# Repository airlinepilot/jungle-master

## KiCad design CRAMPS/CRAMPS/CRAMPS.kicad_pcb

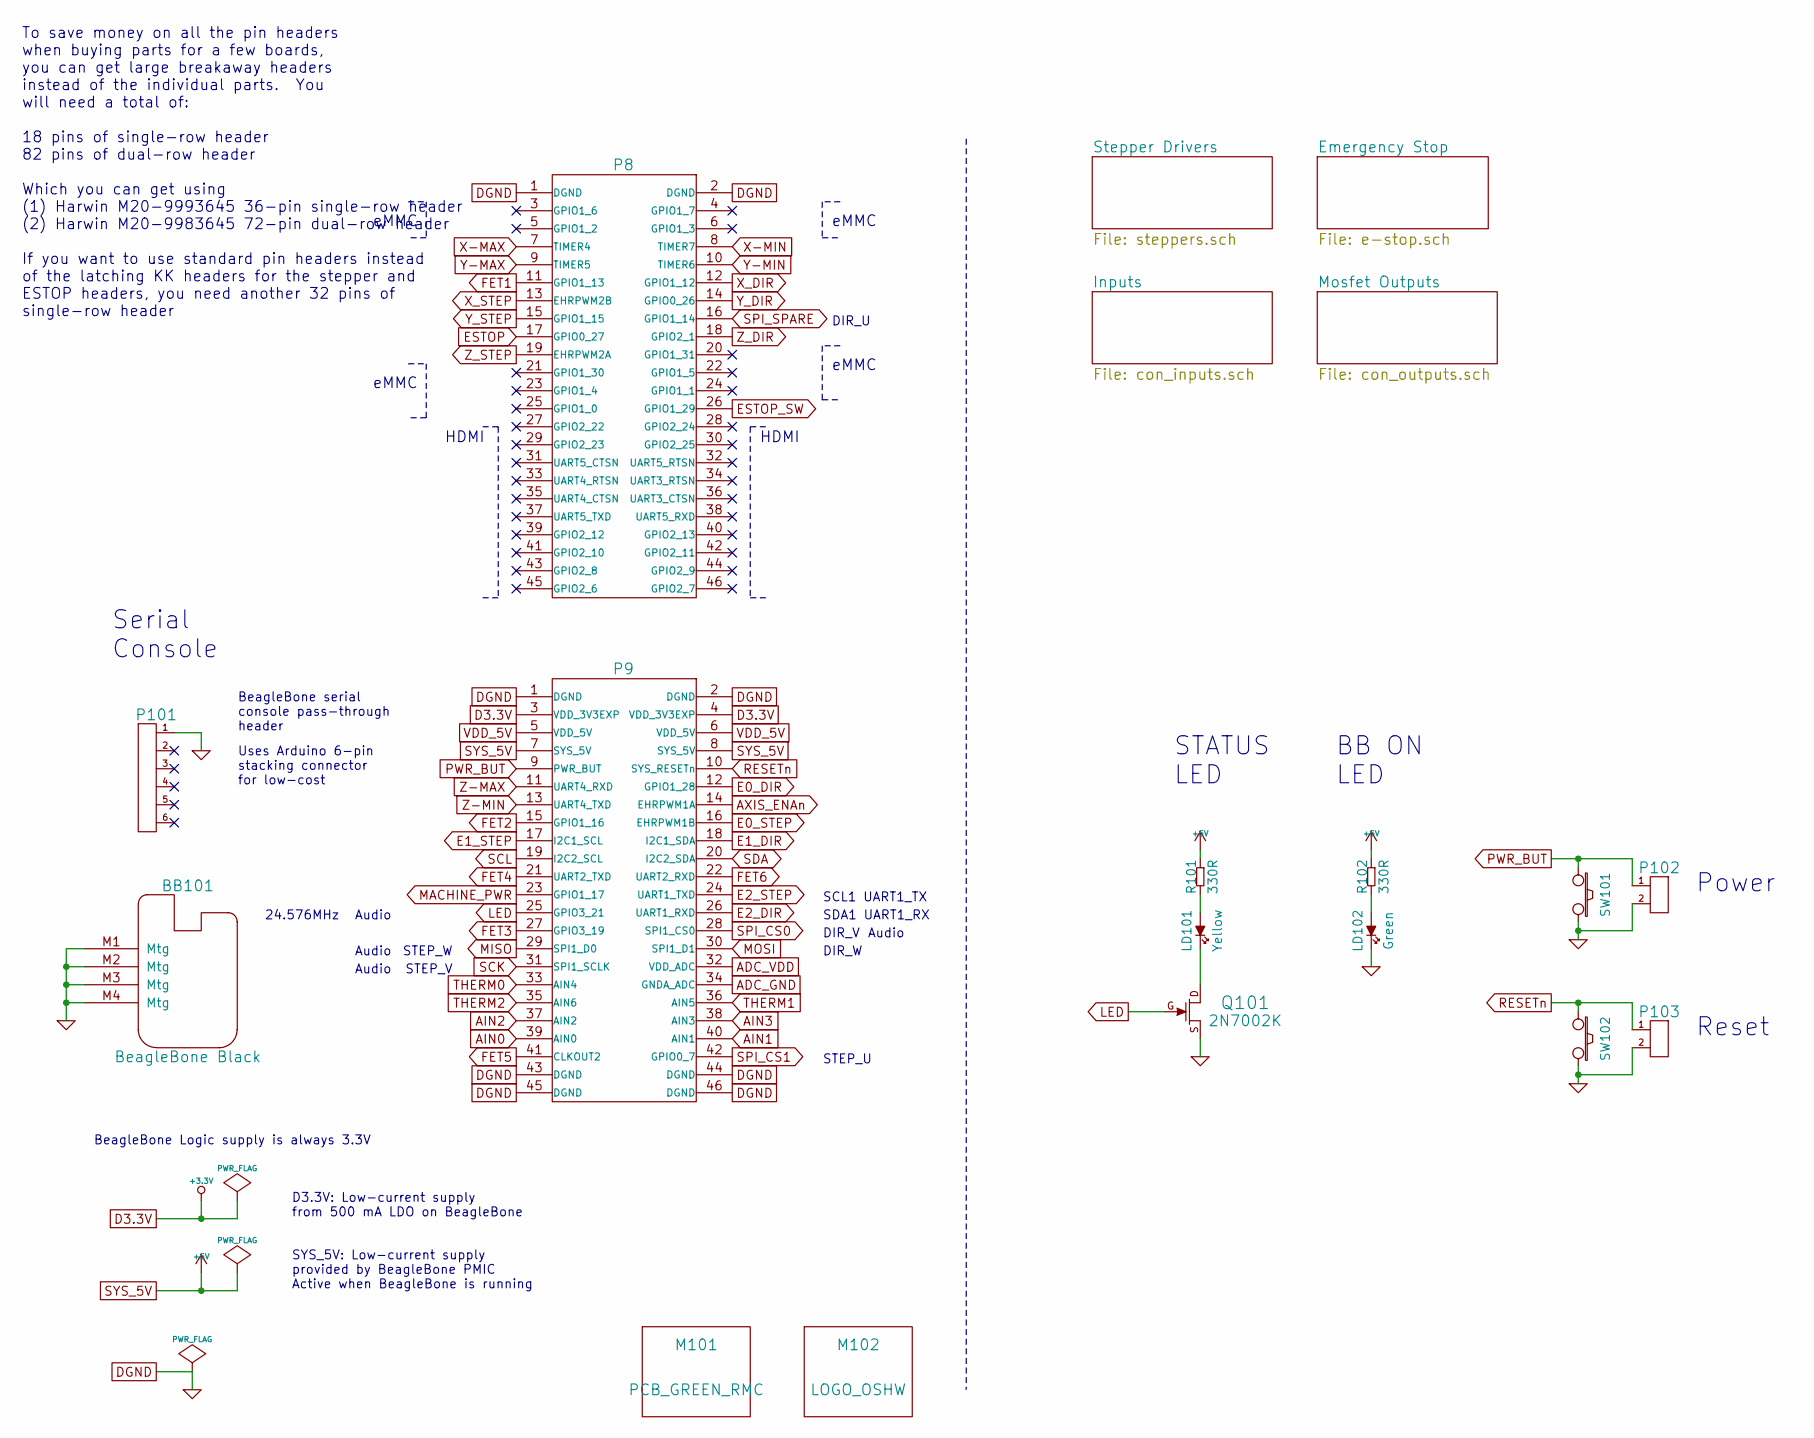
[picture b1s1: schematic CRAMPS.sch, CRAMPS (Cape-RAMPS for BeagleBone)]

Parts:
BB101: BeagleBone Black; BeagleBone-Pins; PartNo BB-BBLK-000
LD101: Yellow; OSRAM-LED-0603; PartNo LY Q976-P1S2-36
LD102: Green; OSRAM-LED-0603; PartNo LG Q971-KN-1
M101: PCB_GREEN_RMC; OSHW_logo_2; PartNo Part of PCB
M102: LOGO_OSHW; PCB_GREEN_RMC; PartNo Part of PCB
P8, P9: BB_EXP_CONN; P8P9_PinHeader; PartNo TSHC-123-D-06-240-GT-LF
P101: SOCKET_6_LONG; pin_strip_6; PartNo PRT-09280
P102, P103: HEADER_2; pin_strip_2; PartNo M20-9990245
Q101: 2N7002K; SOT23GDS; PartNo 2N7002K-7
R101, R102: 330R; RESC1608x55N; PartNo RMCF0603FT330R
SW101, SW102: SW_PUSH; SW_6x6_MULTI; PartNo FSM2JH

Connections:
ADC_GND: P9.34 (GNDA_ADC); also elsewhere on the board
ADC_VDD: P9.32 (VDD_ADC); also elsewhere on the board
AIN0: P9.39 (AIN0); also elsewhere on the board
AIN1: P9.40 (AIN1); also elsewhere on the board
AIN2: P9.37 (AIN2); also elsewhere on the board
AIN3: P9.38 (AIN3); also elsewhere on the board
AXIS_ENAn: P9.14 (EHRPWM1A); also elsewhere on the board
D3.3V: P9.3 (VDD_3V3EXP), P9.4 (VDD_3V3EXP); also elsewhere on the board
E0_DIR: P9.12 (GPIO1_28); also elsewhere on the board
E0_STEP: P9.16 (EHRPWM1B); also elsewhere on the board
E1_DIR: P9.18 (I2C1_SDA); also elsewhere on the board
E1_STEP: P9.17 (I2C1_SCL); also elsewhere on the board
E2_DIR: P9.26 (UART1_RXD); also elsewhere on the board
E2_STEP: P9.24 (UART1_TXD); also elsewhere on the board
ESTOP: P8.17 (GPIO0_27); also elsewhere on the board
ESTOP_SW: P8.26 (GPIO1_29); also elsewhere on the board
FET1: P8.11 (GPIO1_13); also elsewhere on the board
FET2: P9.15 (GPIO1_16); also elsewhere on the board
FET3: P9.27 (GPIO3_19); also elsewhere on the board
FET4: P9.21 (UART2_TXD); also elsewhere on the board
FET5: P9.41 (CLKOUT2); also elsewhere on the board
FET6: P9.22 (UART2_RXD); also elsewhere on the board
LED: P9.25 (GPIO3_21), Q101.G
MACHINE_PWR: P9.23 (GPIO1_17); also elsewhere on the board
MISO: P9.29 (SPI1_D0); also elsewhere on the board
MOSI: P9.30 (SPI1_D1); also elsewhere on the board
unnamed: LD102.A, R102.2
unnamed: LD101.A, R101.2
unnamed: LD101.K, Q101.D
PWR_BUT: P9.9 (PWR_BUT), P102.1, SW101.1
RESETn: P9.10 (SYS_RESETn), P103.1, SW102.1
SCK: P9.31 (SPI1_SCLK); also elsewhere on the board
SCL: P9.19 (I2C2_SCL); also elsewhere on the board
SDA: P9.20 (I2C2_SDA); also elsewhere on the board
SPI_CS0: P9.28 (SPI1_CS0); also elsewhere on the board
SPI_CS1: P9.42 (GPIO0_7); also elsewhere on the board
SPI_SPARE: P8.16 (GPIO1_14); also elsewhere on the board
SYS_5V: P9.7 (SYS_5V), P9.8 (SYS_5V), R101.1, R102.1; also elsewhere on the board
THERM0: P9.33 (AIN4); also elsewhere on the board
THERM1: P9.36 (AIN5); also elsewhere on the board
THERM2: P9.35 (AIN6); also elsewhere on the board
X-MAX: P8.7 (TIMER4); also elsewhere on the board
X-MIN: P8.8 (TIMER7); also elsewhere on the board
X_DIR: P8.12 (GPIO1_12); also elsewhere on the board
X_STEP: P8.13 (EHRPWM2B); also elsewhere on the board
Y-MAX: P8.9 (TIMER5); also elsewhere on the board
Y-MIN: P8.10 (TIMER6); also elsewhere on the board
Y_DIR: P8.14 (GPIO0_26); also elsewhere on the board
Y_STEP: P8.15 (GPIO1_15); also elsewhere on the board
Z-MAX: P9.11 (UART4_RXD); also elsewhere on the board
Z-MIN: P9.13 (UART4_TXD); also elsewhere on the board
Z_DIR: P8.18 (GPIO2_1); also elsewhere on the board
Z_STEP: P8.19 (EHRPWM2A); also elsewhere on the board

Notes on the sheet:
STATUS LED
HDMI
eMMC
24.576MHz
Audio
BeagleBone serial console pass-through header
SCL1 UART1_TX
SDA1 UART1_RX
To save money on all the pin headers when buying parts for a few boards, you can get large breakaway headers instead of the individual parts. You will need a total of: 18 pins of single-row header 82 pins of dual-row header Which you can get using (1) Harwin M20-9993645 36-pin single-row header (2)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
BB ON LED
BeagleBone Logic supply is always 3.3V
SYS_5V: Low-current supply provided by BeagleBone PMIC Active when BeagleBone is running
D3.3V: Low-current supply from 500 mA LDO on BeagleBone
Serial Console
Uses Arduino 6-pin stacking connector for low-cost
Power
Reset
STEP_U
STEP_V
STEP_W
DIR_U
DIR_V
DIR_W

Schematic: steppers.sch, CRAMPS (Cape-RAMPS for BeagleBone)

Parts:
C201, C202, C203, C204, C205, C206: 100u 35V; c_elec_6.3x7.7; PartNo UCD1V101MCL6GS
F201: 10A; Fuse-Loose; PartNo 0297010.WXNV
FH201: FUSE-HOLDER; Keystone-3568; PartNo 3568
JP201, JP202, JP203, JP204, JP205, JP206: HEADER_3X2; pin_strip_3x2; PartNo M20-9980345
P201: PT_2,5-2-5,0-H; PartNo 1935776
P202, P203, P204, P205, P206, P207: KK-2.54-4W; CONN_KK_2.54_4W; PartNo 22-23-2041
P208, P209, P210, P211: POLOLU_SOCKET; Pololu_Socket; PartNo PPTC241LFBN-RC
R201, R202, R203, R204, R205, R206: 100k; RESC1608x55N; PartNo RMCF0603FT100K
S201, S202, S203, S204, S205, S206, S207, S208, S209, S210, S211, S212, S213, S214, S215, S216, S217, S218: SHUNT; Shunt; PartNo 382811-8
U201, U202, U203, U204, U205, U206: Pololu; POLOLU; PartNo DRV8825

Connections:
+V_MOTOR: C201.1, C202.1, C203.1, C204.1, C205.1, C206.1, FH201.3, FH201.4, U201.16, U202.16, U203.16, U204.16, U205.16, U206.16; also elsewhere on the board
/Stepper Drivers/E01A: P205.3, U204.12
/Stepper Drivers/E01B: P205.4, U204.11
/Stepper Drivers/E02A: P205.2, U204.13
/Stepper Drivers/E02B: P205.1, U204.14
/Stepper Drivers/E11A: P206.3, U205.12
/Stepper Drivers/E11B: P206.4, U205.11
/Stepper Drivers/E12A: P206.2, U205.13
/Stepper Drivers/E12B: P206.1, U205.14
/Stepper Drivers/E21A: P207.3, U206.12
/Stepper Drivers/E21B: P207.4, U206.11
/Stepper Drivers/E22A: P207.2, U206.13
/Stepper Drivers/E22B: P207.1, U206.14
/Stepper Drivers/MOT_IN: FH201.1, FH201.2, P201.1
/Stepper Drivers/X1A: P202.3, U201.12
/Stepper Drivers/X1B: P202.4, U201.11
/Stepper Drivers/X2A: P202.2, U201.13
/Stepper Drivers/X2B: P202.1, U201.14
/Stepper Drivers/Y1A: P203.3, U202.12
/Stepper Drivers/Y1B: P203.4, U202.11
/Stepper Drivers/Y2A: P203.2, U202.13
/Stepper Drivers/Y2B: P203.1, U202.14
/Stepper Drivers/Z1A: P204.3, U203.12
/Stepper Drivers/Z1B: P204.4, U203.11
/Stepper Drivers/Z2A: P204.2, U203.13
/Stepper Drivers/Z2B: P204.1, U203.14
D3.3V: JP201.2, JP201.4, JP201.6, JP202.2, JP202.4, JP202.6, JP203.2, JP203.4, JP203.6, JP204.2, JP204.4, JP204.6, JP205.2, JP205.4, JP205.6, JP206.2, JP206.4, JP206.6, U201.5, U201.6, U201.10, U202.5, U202.6, U202.10, U203.5, U203.6, U203.10, U204.5, U204.6, U204.10, U205.5, U205.6, U205.10, U206.5, U206.6, U206.10; also elsewhere on the board
E0_DIR: U204.8; also elsewhere on the board
E0_EN_BUFn: U201.1, U202.1, U203.1, U204.1, U205.1, U206.1; also elsewhere on the board
E0_STEP: U204.7; also elsewhere on the board
E1_DIR: U205.8; also elsewhere on the board
E1_STEP: U205.7; also elsewhere on the board
E2_DIR: U206.8; also elsewhere on the board
E2_STEP: U206.7; also elsewhere on the board
unnamed: JP202.5, U202.4
unnamed: JP201.5, U201.4
unnamed: JP201.3, U201.3
unnamed: JP205.5, U205.4
unnamed: JP205.3, U205.3
unnamed: JP204.5, U204.4
unnamed: JP204.3, U204.3
unnamed: JP201.1, R201.1, U201.2
unnamed: JP206.3, U206.3
unnamed: JP206.5, U206.4
unnamed: JP202.1, R202.1, U202.2
unnamed: JP203.1, R203.1, U203.2
unnamed: JP205.1, R205.1, U205.2
unnamed: JP204.1, R204.1, U204.2
unnamed: JP206.1, R206.1, U206.2
unnamed: JP203.5, U203.4
unnamed: JP203.3, U203.3
unnamed: JP202.3, U202.3
X_DIR: U201.8; also elsewhere on the board
X_STEP: U201.7; also elsewhere on the board
Y_DIR: U202.8; also elsewhere on the board
Y_STEP: U202.7; also elsewhere on the board
Z_DIR: U203.8; also elsewhere on the board
Z_STEP: U203.7; also elsewhere on the board

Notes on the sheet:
Motor Power 12-24V, 10A
24-pin Single-Row sockets for Pololus
Shunts to set micro-stepping

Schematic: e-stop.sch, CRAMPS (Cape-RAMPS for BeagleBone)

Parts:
C301, C302: 100n; CAPC1608x55N; PartNo GRM188R71C104KA01D
JP301: HEADER_2X2; pin_strip_2x2; PartNo M20-9980245
LD301: Green; OSRAM-LED-0603; PartNo LG Q971-KN-1
LD302: Red; OSRAM-LED-0603; PartNo LS Q976-NR-1
P301: HEADER_2; pin_strip_2; PartNo M20-9990245
P302: KK-2.54-2W; CONN_KK_2.54_2W; PartNo 22-23-2021
P303: HEADER_4X2; pin_strip_4x2; PartNo M20-9980445
P304: HEADER_3X2; pin_strip_3x2; PartNo M20-9980345
P305: HEADER_6; pin_strip_6; PartNo M20-9990645
Q301, Q302, Q303, Q304, Q305: 2N7002K; SOT23GDS; PartNo 2N7002K-7
R301, R308, R309, R310, R311, R312, R313, R315, R316: 10k; RESC1608x55N; PartNo RMCF0603FT10K0
R302: 2K7; RESC1608x55N; PartNo RMCF0603FT2K70
R303: 330R; RESC1608x55N; PartNo RMCF0603FT330R
R304, R306, R307, R314: 4k7; RESC1608x55N; PartNo RMCF0603FT4K70
R305: 220R; RESC1608x55N; PartNo RMCF0603FT220R
S301: SHUNT; Shunt; PartNo 382811-8
U301: 24C256; SOIC127P600X175-8AN; PartNo CAT24C256WI-GT3
U302: 74ACT244; SOIC127P1032X265-20N; PartNo 74ACT244SCX

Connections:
+V_MOTOR: P304.1, P304.3, P304.5; also elsewhere on the board
/Emergency Stop/MACHINE_PWRn: LD301.K, Q304.D, R308.2, U302.1 (~1G), U302.19 (~2G)
/Emergency Stop/PS-On: P301.1, Q302.D
ADC_GND: P305.5; also elsewhere on the board
ADC_VDD: P305.6; also elsewhere on the board
AIN0: P305.4; also elsewhere on the board
AIN1: P305.2; also elsewhere on the board
AIN2: P305.1; also elsewhere on the board
AIN3: P305.3; also elsewhere on the board
AXIS_ENAn: U302.2 (1A1), U302.4 (1A2); also elsewhere on the board
D3.3V: C301.1, JP301.1, JP301.3, P303.2, R301.1, R304.1, R305.1, R306.1, R307.1, R310.1, R314.1, U301.3 (A2), U301.8 (VCC); also elsewhere on the board
E0_EN_BUFn: R314.2, U302.18 (1Y1); also elsewhere on the board
EN_CRAMP3n: P303.8, R310.2, U302.16 (1Y2)
ESTOP: R302.2; also elsewhere on the board
ESTOP_SW: Q301.G; also elsewhere on the board
FET1: U302.17 (2A4); also elsewhere on the board
FET1_BUF: R309.1, U302.3 (2Y4); also elsewhere on the board
FET2: U302.15 (2A3); also elsewhere on the board
FET2_BUF: R311.1, U302.5 (2Y3); also elsewhere on the board
FET3: U302.13 (2A2); also elsewhere on the board
FET3_BUF: R312.1, U302.7 (2Y2); also elsewhere on the board
FET4: U302.11 (2A1); also elsewhere on the board
FET4_BUF: R313.1, U302.9 (2Y1); also elsewhere on the board
FET5: U302.6 (1A3); also elsewhere on the board
FET5_BUF: R316.1, U302.14 (1Y3); also elsewhere on the board
FET6: U302.8 (1A4); also elsewhere on the board
FET6_BUF: R315.1, U302.12 (1Y4); also elsewhere on the board
MACHINE_PWR: Q302.G, Q304.G; also elsewhere on the board
unnamed: JP301.2, U301.7 (WP)
unnamed: LD302.A, R305.2
unnamed: P302.1, Q302.S, Q304.S, Q305.G, R302.1, R304.2
unnamed: LD302.K, Q305.D
unnamed: Q301.D, Q303.G, R301.2
unnamed: P302.2, Q303.D
unnamed: LD301.A, R303.2
unnamed: JP301.4, U301.1 (A0)
SCL: P303.3, R306.2, U301.6 (SCL); also elsewhere on the board
SDA: P303.5, R307.2, U301.5 (SDA); also elsewhere on the board
SPI_CS1: P303.4; also elsewhere on the board
SPI_SPARE: P303.6; also elsewhere on the board
SYS_5V: C302.1, P303.1, R303.1, R308.1, U302.20 (VDD); also elsewhere on the board

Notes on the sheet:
Emergency Stop switch (Normally Closed type) use shunt if not present
Active low
Active high
Must use ACT type buffer with 24 mA output drive Inputs are compatible with 3.3V or 5V logic
Each Pololu has a 100K pull-down on the enable line. Make sure the pull up will reach a valid logic level (2.2V or more) with multiple enables paralleled.
ESTOP Active (high) unless: * ESTOP chain is unbroken * Software is driving ESTOP_SW low
Machine Power Status LED
EEPROM
Address and WP pins have internal pull-down Default configuration is no shunts populated: Addr = 0xA8 WP = Disabled (writes allowed)
I2C and misc signals
Analog
Resistive Touch Screen
ATX Power On
Two FETs used to keep ESTOP polarity consistent with V1.0
ESTOP
Place a shunt on ESTOP header by default, for folks who do not have an off-board ESTOP switch
Motor Power
CRAMP3 Expansion
Series resistor on ESTOPn provides some protection from ESTOP chain FETs protect against high voltage from PS_ON or MACHINE_PWRn feeding back to the 3.3V 'Bone
ACTIVE
Status LED
STEP_U
DIR_U

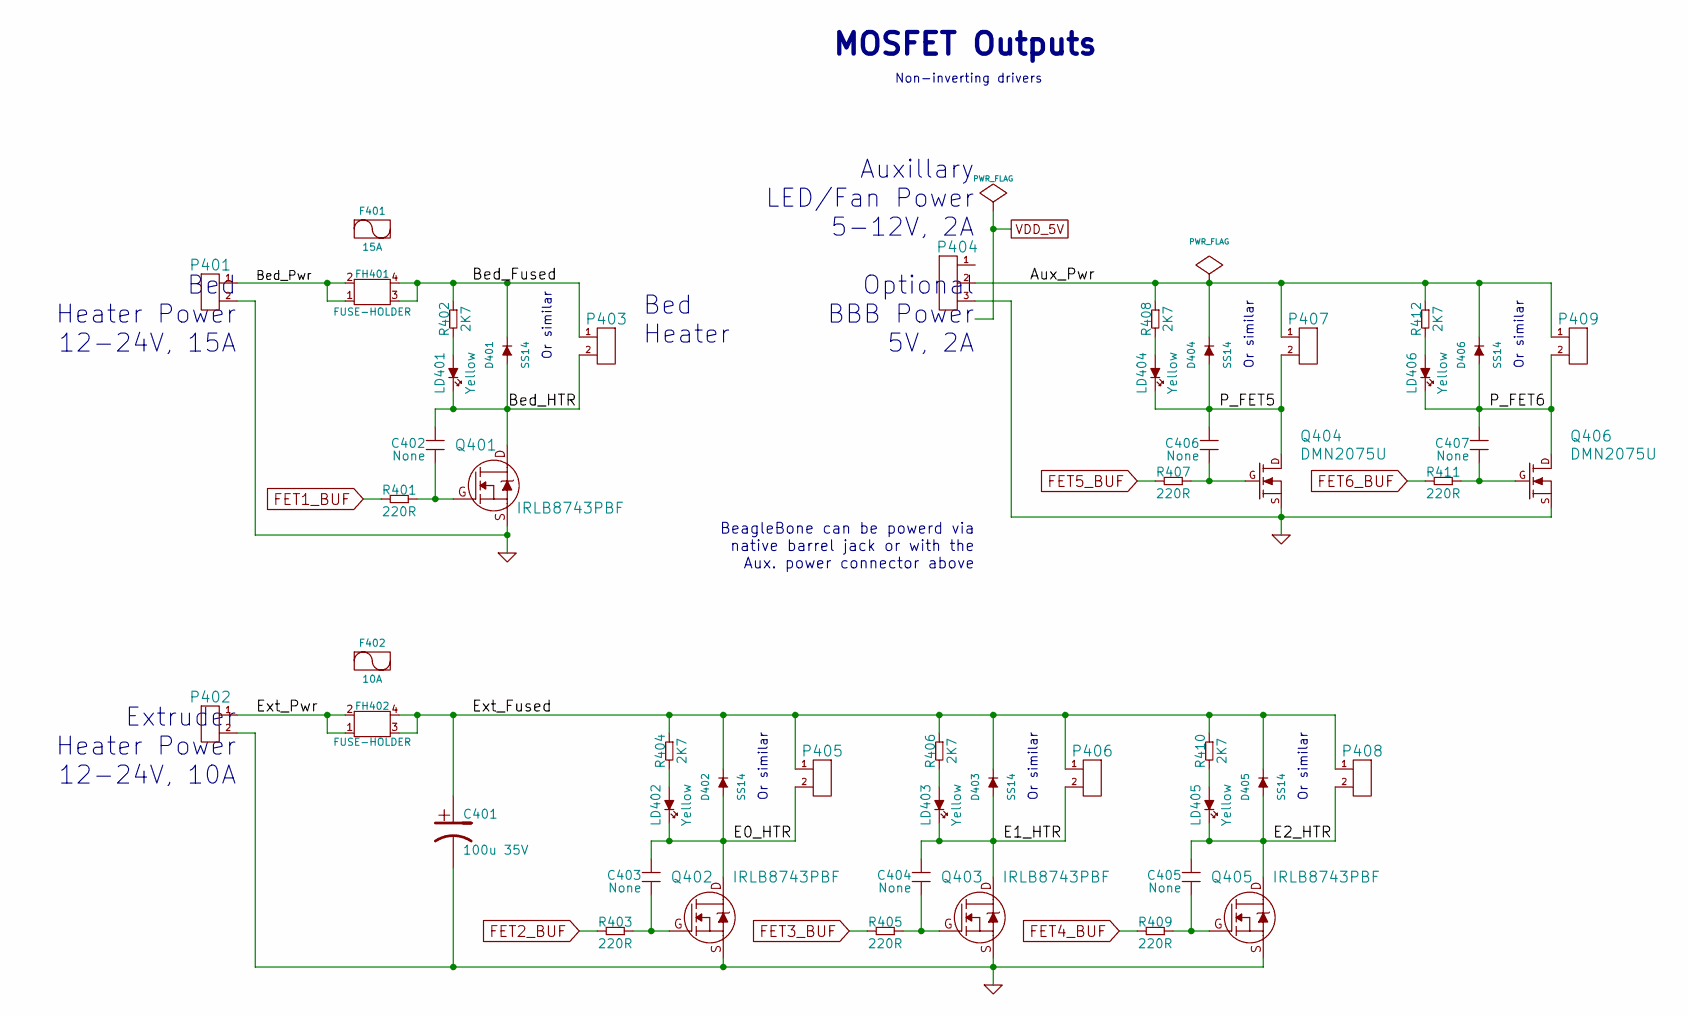
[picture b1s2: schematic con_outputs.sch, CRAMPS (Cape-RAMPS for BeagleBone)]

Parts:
C401: 100u 35V; c_elec_6.3x7.7; PartNo UCD1V101MCL6GS
C402, C403, C404, C405, C406, C407: None; CAPC1608x55N; PartNo Do Not Populate
D401, D402, D403, D404, D405, D406: SS14; DIOM5127X229N; PartNo SS14-E3/61T
F401: 15A; Fuse-Loose; PartNo 0297015.WXNV
F402: 10A; Fuse-Loose; PartNo 0297010.WXNV
FH401, FH402: FUSE-HOLDER; Keystone-3568; PartNo 3568
LD401, LD402, LD403, LD404, LD405, LD406: Yellow; OSRAM-LED-0603; PartNo LY Q976-P1S2-36
P401, P402, P403: PT_2,5-2-5,0-H; PartNo 1935776
P404: PT_1,5-3-3,5-H; PartNo 1984620
P405, P406, P408: PT_1,5-2-3,5-H; PartNo 1984617
P407, P409: KK-2.54-2W; CONN_KK_2.54_2W; PartNo 22-23-2021
Q401, Q402, Q403, Q405: IRLB8743PBF; TO-220AB_IRF2804_RMC; PartNo IRLB8743PBF
Q404, Q406: DMN2075U; SOT23GDS; PartNo DMN2075U-7
R401, R403, R405, R407, R409, R411: 220R; RESC1608x55N; PartNo RMCF0603FT220R
R402, R404, R406, R408, R410, R412: 2K7; RESC1608x55N; PartNo RMCF0603FT2K70

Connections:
/Mosfet Outputs/Bed_Fused: D401.K, FH401.3, FH401.4, P403.1, R402.1
/Mosfet Outputs/Bed_HTR: C402.1, D401.A, LD401.K, P403.2, Q401.D
/Mosfet Outputs/Bed_Pwr: FH401.1, FH401.2, P401.1
/Mosfet Outputs/E0_HTR: C403.1, D402.A, LD402.K, P405.2, Q402.D
/Mosfet Outputs/E1_HTR: C404.1, D403.A, LD403.K, P406.2, Q403.D
/Mosfet Outputs/E2_HTR: C405.1, D405.A, LD405.K, P408.2, Q405.D
/Mosfet Outputs/Ext_Fused: C401.1, D402.K, D403.K, D405.K, FH402.3, FH402.4, P405.1, P406.1, P408.1, R404.1, R406.1, R410.1
/Mosfet Outputs/Ext_Pwr: FH402.1, FH402.2, P402.1
/Mosfet Outputs/P_FET5: C406.1, D404.A, LD404.K, P407.2, Q404.D
/Mosfet Outputs/P_FET6: C407.1, D406.A, LD406.K, P409.2, Q406.D
FET1_BUF: R401.2; also elsewhere on the board
FET2_BUF: R403.2; also elsewhere on the board
FET3_BUF: R405.2; also elsewhere on the board
FET4_BUF: R409.2; also elsewhere on the board
FET5_BUF: R407.2; also elsewhere on the board
FET6_BUF: R411.2; also elsewhere on the board
unnamed: LD402.A, R404.2
unnamed: LD405.A, R410.2
unnamed: LD404.A, R408.2
unnamed: LD403.A, R406.2
unnamed: LD401.A, R402.2
unnamed: LD406.A, R412.2
unnamed: C404.2, Q403.G, R405.1
unnamed: C403.2, Q402.G, R403.1
unnamed: C407.2, Q406.G, R411.1
unnamed: C406.2, Q404.G, R407.1
unnamed: C402.2, Q401.G, R401.1
unnamed: C405.2, Q405.G, R409.1

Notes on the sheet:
Non-inverting drivers
MOSFET Outputs
Or similar
Bed Heater Power 12-24V, 15A
Bed Heater
Extruder Heater Power 12-24V, 10A
Auxillary LED/Fan Power 5-12V, 2A Optional BBB Power 5V, 2A
BeagleBone can be powerd via native barrel jack or with the Aux. power connector above

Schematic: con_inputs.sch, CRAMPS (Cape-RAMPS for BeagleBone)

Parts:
C501, C502, C503, C504, C505: 100n; CAPC1608x55N; PartNo GRM188R71C104KA01D
C506, C507, C508, C509: 10u; CAPC1608x55N; PartNo JMK107ABJ106MAHT
JP501: HEADER_2; pin_strip_2; PartNo M20-9990245
P501: HEADER_6; pin_strip_6; PartNo M20-9990645
P502: HEADER_6X2; pin_strip_6x2; PartNo M20-9980645
P503, P504: HEADER_4X2; pin_strip_4x2; PartNo M20-9980445
R501, R502, R503, R504, R505, R506, R507, R508, R509, R510: 10k; RESC1608x55N; PartNo RMCF0603FT10K0
R511, R512, R513, R514: 2K0 1%; RESC1608x55N; PartNo RMCF0603FT2K00
R515, R516, R517, R518: 4k7; RESC1608x55N; PartNo RMCF0603FT4K70
S501: SHUNT; Shunt; PartNo 382811-8
U501: 74CBTD3861; SOIC127P1030X265-24N

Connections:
/Inputs/MISO-5V: P503.2, R507.2, U501.8 (A7)
/Inputs/MOSI-5V: P503.6, R509.2, U501.10 (A9)
/Inputs/SCK-5V: P503.4, R508.2, U501.9 (A8)
/Inputs/SPI_CS0-5V: P503.8, R510.2, U501.11 (A10)
ADC_GND: C502.2, C503.2, C504.2, C505.2, C506.2, C507.2, C508.2, C509.2, P504.1, P504.3, P504.5, P504.7; also elsewhere on the board
ADC_VDD: R511.1, R512.1, R513.1, R514.1; also elsewhere on the board
AIN3: JP501.2; also elsewhere on the board
MISO: U501.16 (B7); also elsewhere on the board
MOSI: U501.14 (B9); also elsewhere on the board
unnamed: P504.4, R513.2, R517.2
unnamed: P504.8, R511.2, R515.2
unnamed: P504.2, R514.2, R518.2
unnamed: P502.4, R502.2, U501.3 (A2)
unnamed: P502.6, R503.2, U501.4 (A3)
unnamed: P502.8, R504.2, U501.5 (A4)
unnamed: P502.10, R505.2, U501.6 (A5)
unnamed: P502.12, R506.2, U501.7 (A6)
unnamed: P502.2, R501.2, U501.2 (A1)
unnamed: P504.6, R512.2, R516.2
SCK: U501.15 (B8); also elsewhere on the board
SPI_CS0: U501.13 (B10); also elsewhere on the board
SYS_5V: C501.1, P501.1, P501.2, P501.3, P501.4, P501.5, P501.6, R501.1, R502.1, R503.1, R504.1, R505.1, R506.1, R507.1, R508.1, R509.1, R510.1, U501.24 (VCC); also elsewhere on the board
THERM0: C502.1, C506.1, R515.1; also elsewhere on the board
THERM1: C503.1, C507.1, R516.1; also elsewhere on the board
THERM2: C504.1, C508.1, R517.1; also elsewhere on the board
THERM3: C505.1, C509.1, JP501.1, R518.1
X-MAX: U501.21 (B2); also elsewhere on the board
X-MIN: U501.22 (B1); also elsewhere on the board
Y-MAX: U501.19 (B4); also elsewhere on the board
Y-MIN: U501.20 (B3); also elsewhere on the board
Z-MAX: U501.17 (B6); also elsewhere on the board
Z-MIN: U501.18 (B5); also elsewhere on the board

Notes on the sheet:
Endstop inputs are 5V tolerant and may also be used as 3.3V output signals if desired
Endstops
From Thermistors
Thermistor Inputs
Shunt populated by default Remove to support 4-wire touch-screen using AIN 0-3
To ADC Inputs
P503 may be used for: * Additional digital I/O * CRAMP3 add-on board * SPI expansion
STEP_V
STEP_W
DIR_V
DIR_W

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
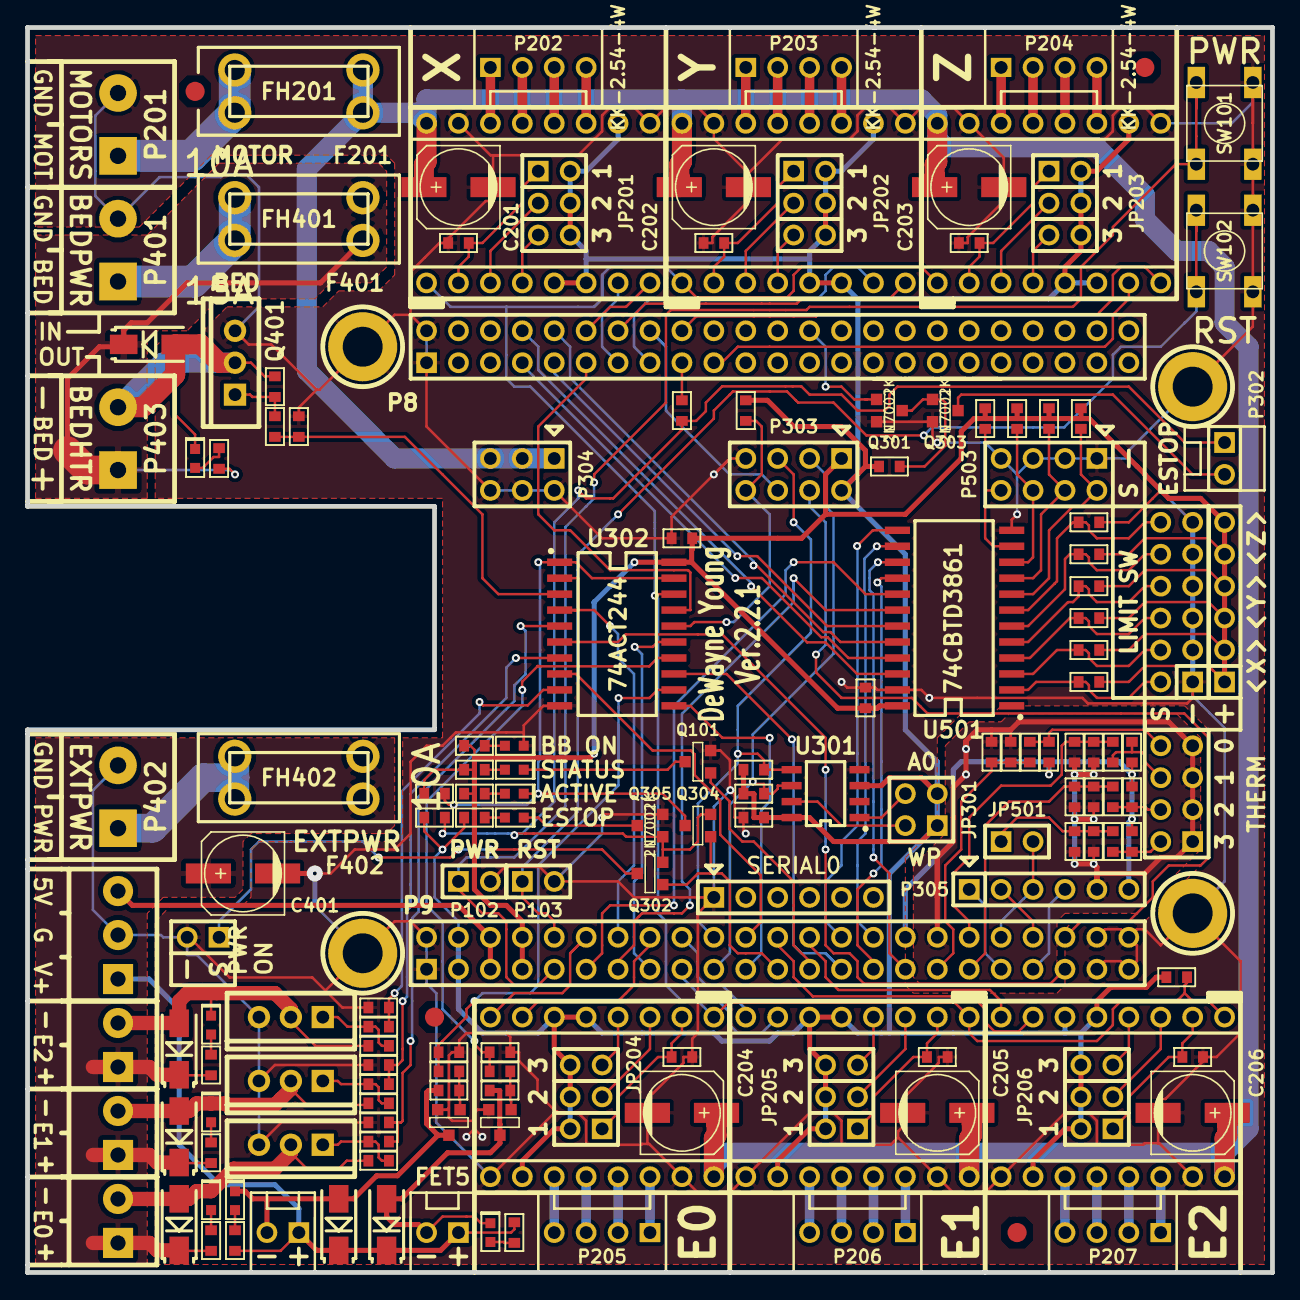
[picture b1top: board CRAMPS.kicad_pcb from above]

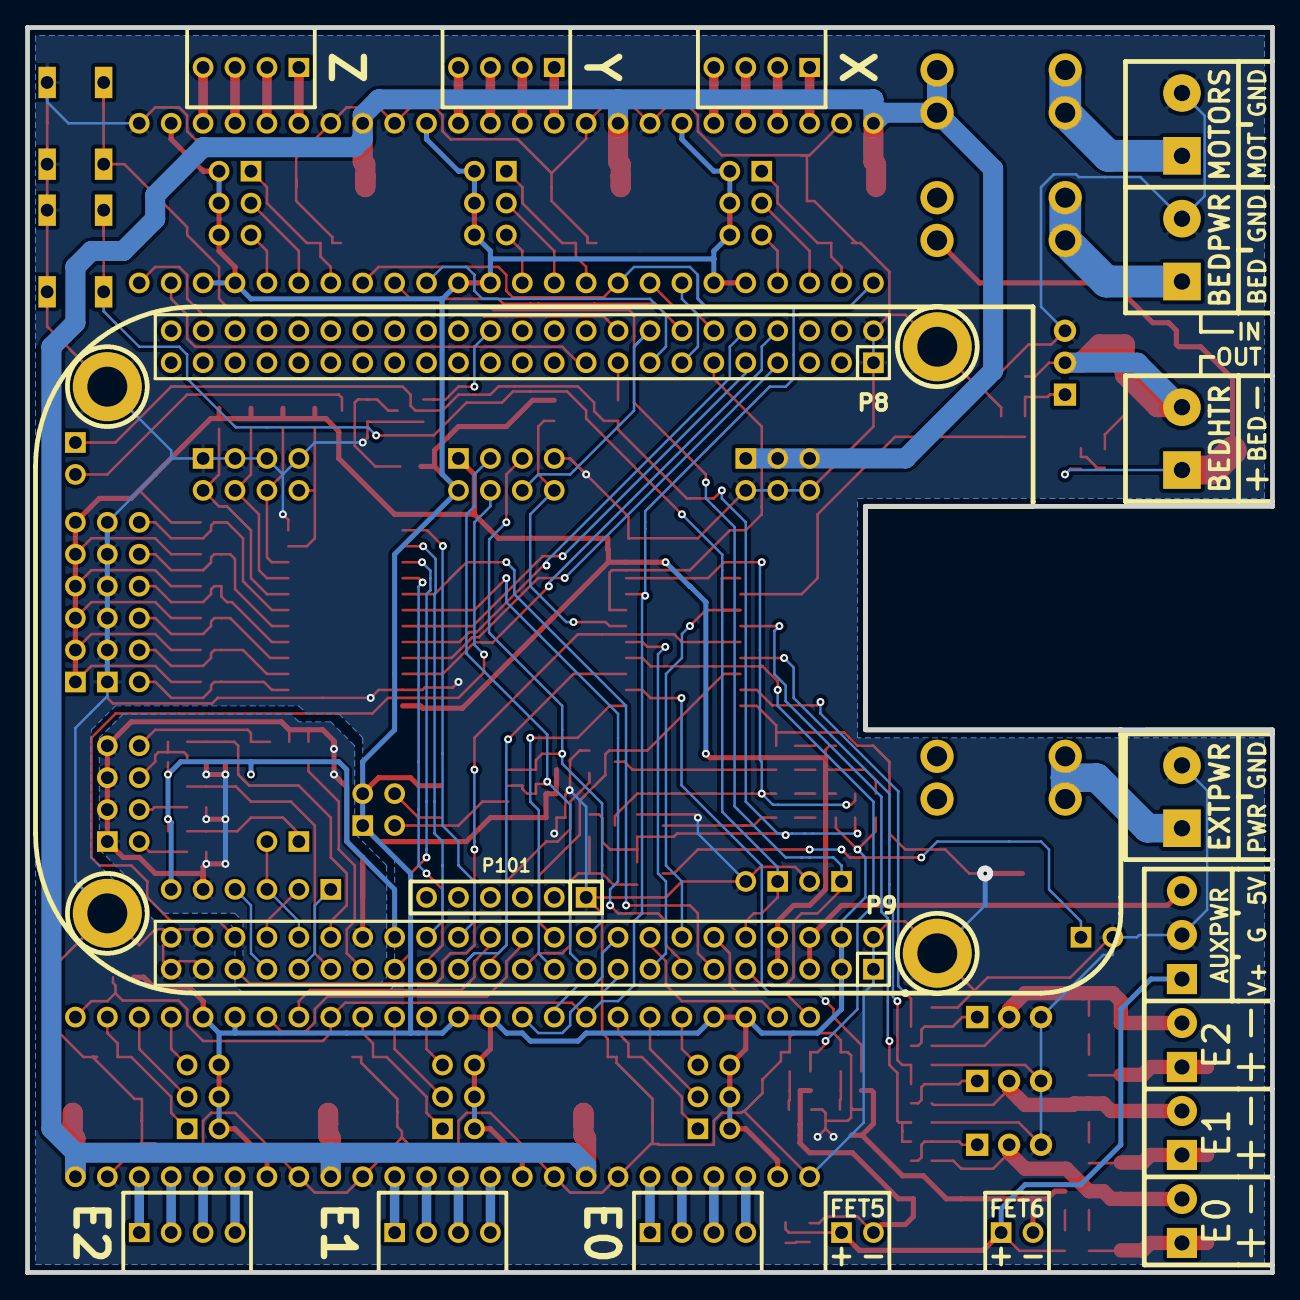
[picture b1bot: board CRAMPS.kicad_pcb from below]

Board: 2 copper layers, 99.1 x 99.1 mm, 191 parts (4 on the bottom side), 155 nets.

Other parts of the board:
FID1, FID2, FID3, FID4: VAL**; FIDUCIAL-060

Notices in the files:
CRAMPS/CRAMPS/CRAMPS.kicad_pcb:
Copyright 2014 GPL v3
